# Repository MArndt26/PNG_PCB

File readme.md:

# PNG Datalogger PCB

## Resources
Teensy Schematic Library:
https://github.com/XenGi/teensy_library

Teensy Footprint Library:
https://github.com/XenGi/teensy.pretty

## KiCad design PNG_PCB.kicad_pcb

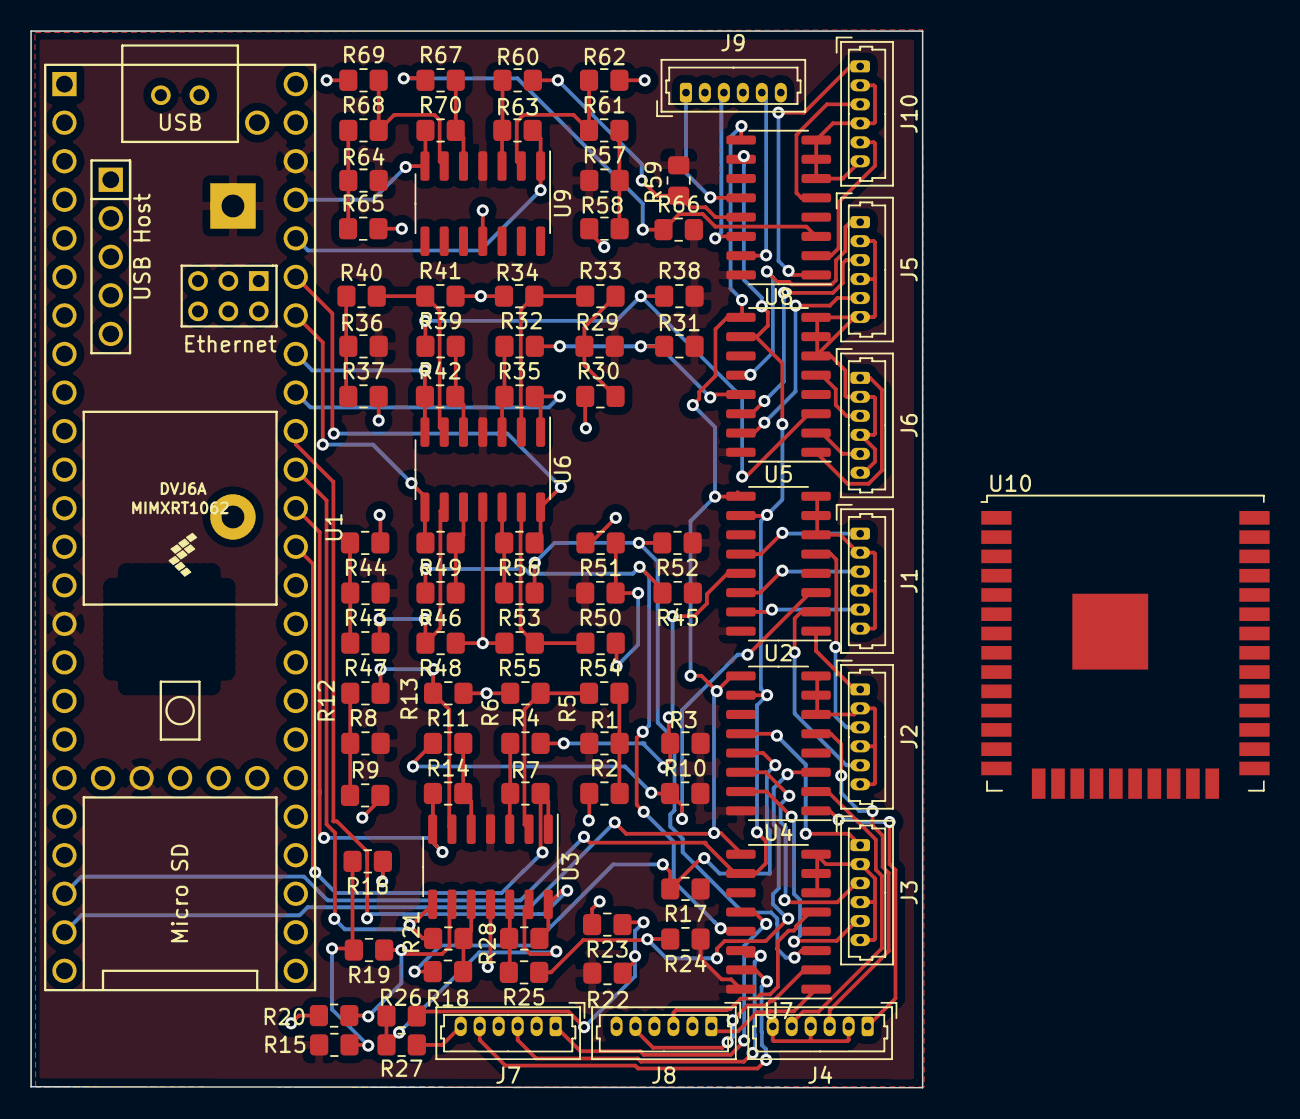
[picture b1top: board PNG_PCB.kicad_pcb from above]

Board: 2 copper layers, 58.7 x 69.6 mm, 91 parts (1 on the bottom side), 85 nets.

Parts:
BT1: Battery_Cell; BatteryHolder_Keystone_103_1x20mm
J1, J2, J3, J4, J5, J6, J7, J8, J9, J10: Conn_01x06_Female; Molex_PicoBlade_53047-0610_1x06_P1.25mm_Vertical
R1, R3, R8, R10, R15, R17, R22, R24, R29, R31, R36, R38, R43, R45, R50, R52, R57, R59, R64, R66: 560; R_0805_2012Metric_Pad1.20x1.40mm_HandSolder
R2, R9, R16, R23, R30, R37, R44, R51, R58, R65: 300; R_0805_2012Metric_Pad1.20x1.40mm_HandSolder
R4, R5, R11, R12, R18, R19, R25, R26, R32, R33, R39, R40, R46, R47, R53, R54, R60, R61, R67, R68: 1; R_0805_2012Metric_Pad1.20x1.40mm_HandSolder
R6, R7, R13, R14, R20, R21, R27, R28, R34, R35, R41, R42, R48, R49, R55, R56, R62, R63, R69, R70: 15; R_0805_2012Metric_Pad1.20x1.40mm_HandSolder
U1: Teensy4.1; Teensy41
U2, U4, U5, U7, U8: Mux; SOIC-16_3.9x9.9mm_P1.27mm
U3, U6, U9: MCP6004; SOIC-14_3.9x8.7mm_P1.27mm
U10: ESP32-WROOM-32U

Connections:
+3V3: BT1.1, R1.1, R3.1, R8.1, R10.1, R15.1, R17.1, R22.1, R24.1, R29.1, R31.1, R36.1, R38.1, R43.1, R45.1, R50.1, R52.1, R57.1, R59.1, R64.1, R66.1, U1.15, U1.46, U1.51, U2.16, U3.4, U4.16, U5.16, U6.4, U7.16, U8.16, U9.4
/ADC_IN_0: R7.1, U1.36, U3.1
/ADC_IN_1: R14.1, U1.37, U3.7
/ADC_IN_2: R21.1, U1.38, U3.8
/ADC_IN_3: R28.1, U1.39, U3.14
/ADC_IN_4: R35.1, U1.40, U6.1
/ADC_IN_5: R42.1, U1.41, U6.7
/ADC_IN_6: R49.1, U1.42, U6.8
/ADC_IN_7: R56.1, U1.43, U6.14
/ADC_IN_8: R63.1, U1.44, U9.1
/ADC_IN_9: R70.1, U1.45, U9.7
/ampA0/V1: R3.2, R4.1, U2.13
/ampA0/V2: R1.2, R2.1, R5.2
/ampA0/mux0: J1.1, U2.12
/ampA0/mux1: J1.3, U2.14
/ampA0/mux2: J1.5, U2.15
/ampA1/V1: R31.2, R32.1, U5.13
/ampA1/V2: R29.2, R30.1, R33.2
/ampA1/mux0: J5.1, U5.12
/ampA1/mux1: J5.3, U5.14
/ampA1/mux2: J5.5, U5.15
/ampA2/V1: R59.2, R60.1, U8.13
/ampA2/V2: R57.2, R58.1, R61.2
/ampA2/mux0: J9.1, U8.12
/ampA2/mux1: J9.3, U8.14
/ampA2/mux2: J9.5, U8.15
/ampB0/V1: R10.2, R11.1, U2.3
/ampB0/V2: R8.2, R9.1, R12.2
/ampB0/mux0: J2.1, U2.1
/ampB0/mux1: J2.3, U2.5
/ampB0/mux2: J2.5, U2.2
/ampB1/V1: R38.2, R39.1, U5.3
/ampB1/V2: R36.2, R37.1, R40.2
/ampB1/mux0: J6.1, U5.1
/ampB1/mux1: J6.3, U5.5
/ampB1/mux2: J6.5, U5.2
/ampB2/V1: R66.2, R67.1, U8.3
/ampB2/V2: R64.2, R65.1, R68.2
/ampB2/mux0: J10.1, U8.1
/ampB2/mux1: J10.3, U8.5
/ampB2/mux2: J10.5, U8.2
/ampC0/V1: R17.2, R18.1, U4.13
/ampC0/V2: R15.2, R16.1, R19.2
/ampC0/mux0: J3.1, U4.12
/ampC0/mux1: J3.3, U4.14
/ampC0/mux2: J3.5, U4.15
/ampC1/V1: R45.2, R46.1, U7.13
/ampC1/V2: R43.2, R44.1, R47.2
/ampC1/mux0: J7.1, U7.12
/ampC1/mux1: J7.3, U7.14
/ampC1/mux2: J7.5, U7.15
/ampD0/V1: R24.2, R25.1, U4.3
/ampD0/V2: R22.2, R23.1, R26.2
/ampD0/mux0: J4.1, U4.1
/ampD0/mux1: J4.3, U4.5
/ampD0/mux2: J4.5, U4.2
/ampD1/V1: R52.2, R53.1, U7.3
/ampD1/V2: R50.2, R51.1, R54.2
/ampD1/mux0: J8.1, U7.1
/ampD1/mux1: J8.3, U7.5
/ampD1/mux2: J8.5, U7.2
/selA: U1.22, U2.10, U4.10, U5.10, U7.10, U8.10
/selB: U1.23, U2.9, U4.9, U5.9, U7.9, U8.9
GND: BT1.2, J1.2, J1.4, J1.6, J2.2, J2.4, J2.6, J3.2, J3.4, J3.6, J4.2, J4.4, J4.6, J5.2, J5.4, J5.6, J6.2, J6.4, J6.6, J7.2, J7.4, J7.6, J8.2, J8.4, J8.6, J9.2, J9.4, J9.6, J10.2, J10.4, J10.6, R2.2, R6.2, R9.2, R13.2, R16.2, R20.2, R23.2, R27.2, R30.2, R34.2, R37.2, R41.2, R44.2, R48.2, R51.2, R55.2, R58.2, R62.2, R65.2, R69.2, U1.1, U1.47, U1.52, U1.58, U1.59, U2.6, U2.7, U2.8, U3.11, U4.6, U4.7, U4.8, U5.6, U5.7, U5.8, U6.11, U7.6, U7.7, U7.8, U8.6, U8.7, U8.8, U9.11
unnamed: R4.2, R7.2, U3.3
unnamed: R5.1, R6.1, U3.2
unnamed: R11.2, R14.2, U3.5
unnamed: R12.1, R13.1, U3.6
unnamed: R18.2, R21.2, U3.10
unnamed: R19.1, R20.1, U3.9
unnamed: R25.2, R28.2, U3.12
unnamed: R26.1, R27.1, U3.13
unnamed: R32.2, R35.2, U6.3
unnamed: R33.1, R34.1, U6.2
unnamed: R39.2, R42.2, U6.5
unnamed: R40.1, R41.1, U6.6
unnamed: R46.2, R49.2, U6.10
unnamed: R47.1, R48.1, U6.9
unnamed: R53.2, R56.2, U6.12
unnamed: R54.1, R55.1, U6.13
unnamed: R60.2, R63.2, U9.3
unnamed: R61.1, R62.1, U9.2
unnamed: R67.2, R70.2, U9.5
unnamed: R68.1, R69.1, U9.6
unnamed: U10.1, U10.15, U10.38, U10.39

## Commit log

2021-01-30 added all adc outputs
2021-01-30 added screw terminal port for sync output
2021-01-30 fixed sync output and added sync input
2021-01-30 annotated sync in and out
2021-01-30 added no connects on teensy
2021-01-30 added footprint to some op amps
2021-01-30 added components to pcb
2021-01-30 changed mux package to correct dip 16
2021-01-30 updated all mux packages in eeschema
2021-01-30 added all muxes to the board
2021-01-30 removed todo note
2021-01-30 changed to mcp6004 op amp
2021-01-30 added sensor sheet
2021-01-30 switched to sensor sheet for one sensor divider
2021-01-30 updated screw terminals to 2.54mm
2021-01-30 removed stacked components
2021-01-30 revised sensor connector
2021-01-30 updated docs with datasheets
2021-02-03 removed sync signals
2021-02-03 started working on routing the board
2021-02-07 moved sensor r div to other side of mux
2021-02-07 organized the mux inputs to their respective muxes
2021-02-07 first rough draft for first mux unit
2021-02-10 one amp setup
2021-02-10 top mux and two amps connected up
2021-02-10 top mux connected to final position
2021-02-10 wired up the middle amp
2021-02-10 routed 3rd amp
2021-02-10 placed final location of call components
2021-02-10 routed sel lines to muxes
2021-02-10 all components placed and routed
2021-02-10 added edge cuts and resized board to minimize footprint
2021-02-10 fixed drc errors
2021-02-10 added purdue logo
2021-02-10 generated gerbers and added promo image
2021-02-11 updated image on board
2021-02-17 added image to readme
2021-02-17 removed gerbers from git
2021-05-28 before switching to small branch
2021-05-28 updated mcp6004 footprint on sch
2021-05-28 updated resistors to 0805 on amp.sch
2021-05-28 added mux footprint/datasheet to amp.sch
2021-05-28 updated strain gauge connection to solder pads
2021-05-28 updated sch header
2021-05-28 updated header on board file
2021-05-29 changed solder pads to be two separate footprints
2021-05-29 switched over remaining rs to 0805
2021-05-29 pulled in new parts to pcb
2021-05-29 fixed issue with wrong amp footprint
2021-05-29 added top side of first rework
2021-05-29 finished full of middle amp
2021-05-29 finished 3 amps
2021-05-29 connected adc to amps 1,2,3
2021-05-29 finished amp 4
2021-05-29 finished all amps
2021-05-29 connected up all amps
2021-05-29 reverted back to screw terminals
2021-05-29 changed to 1.00mm screw term holes
2021-05-29 changed connector verbage
2021-05-29 routed first two mux units
2021-05-29 finished but have drc errors for solder holes
2021-05-30 moved some vias for better power plane
2021-05-31 fixed all drc errors before making new connections
2021-05-31 updated sch with pico connectors
2021-05-31 left off reworking bottom of board
2021-06-01 finished routing and fixing drc errors
2021-06-01 added png logo
2021-06-01 copied teensy footprint over to PNG_PCB.pretty
2021-06-01 added 3d model to footprint
2021-06-01 added battery
2021-06-01 left off with esp32 needing integration
